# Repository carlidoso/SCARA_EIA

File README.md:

Repositorio para el codigo y material de utilidad del robot SCARA de la universidad EIA

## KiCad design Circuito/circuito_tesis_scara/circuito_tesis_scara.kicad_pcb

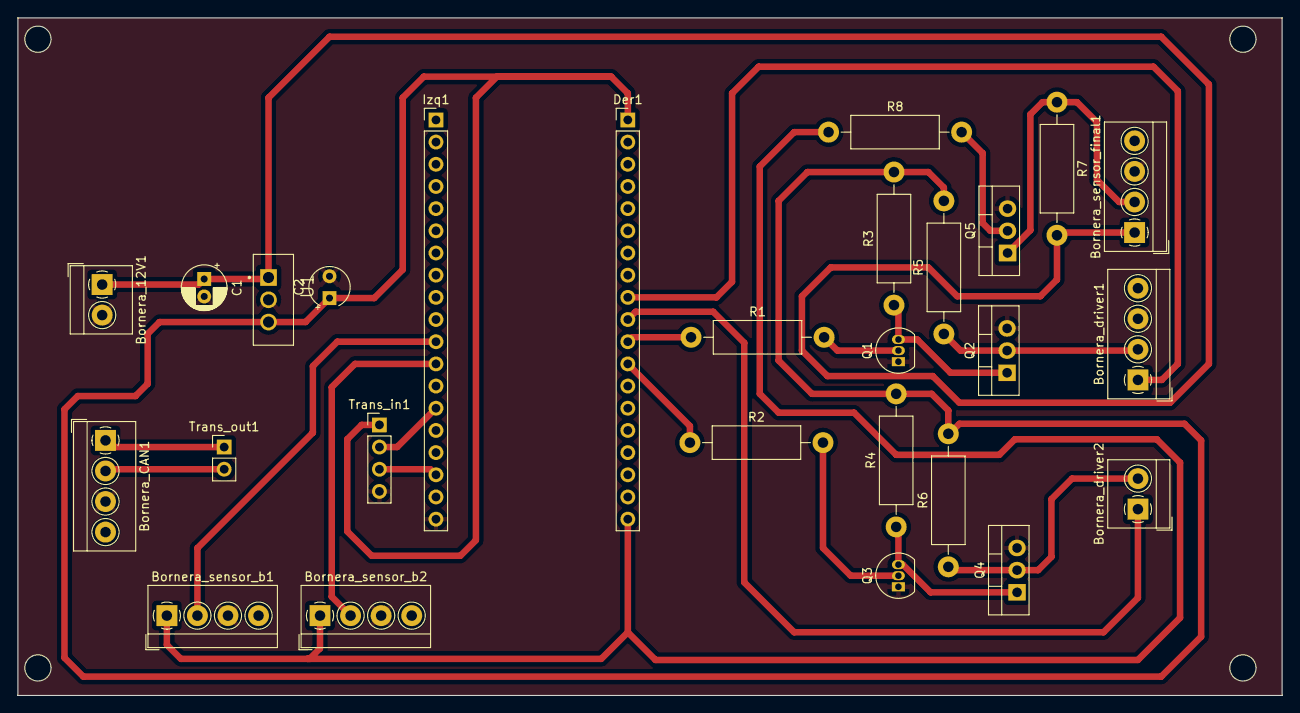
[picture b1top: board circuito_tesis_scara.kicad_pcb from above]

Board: 2 copper layers, 144.8 x 77.6 mm, 27 parts (0 on the bottom side), 22 nets.

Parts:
Bornera_12V1: Screw_Terminal_01x02; TerminalBlock_4Ucon_1x02_P3.50mm_Horizontal
Bornera_CAN1: Screw_Terminal_01x04; TerminalBlock_4Ucon_1x04_P3.50mm_Horizontal
Bornera_driver1: Screw_Terminal_01x04; TerminalBlock_4Ucon_1x04_P3.50mm_Horizontal
Bornera_driver2: Screw_Terminal_01x02; TerminalBlock_4Ucon_1x02_P3.50mm_Horizontal
Bornera_sensor_b1, Bornera_sensor_b2: Screw_Terminal_01x04; TerminalBlock_4Ucon_1x04_P3.50mm_Horizontal
Bornera_sensor_final1: Screw_Terminal_01x04; TerminalBlock_4Ucon_1x04_P3.50mm_Horizontal
C1: C_Polarized; CP_Radial_D5.0mm_P2.00mm
C2: C; CP_Radial_Tantal_D4.5mm_P2.50mm
Der1: Conn_01x19; PinHeader_1x19_P2.54mm_Vertical
Izq1: Conn_01x19; PinHeader_1x19_P2.54mm_Vertical
Q1, Q3: 2N3904; TO-92_Inline
Q2, Q4, Q5: IRF740; TO-220-3_Vertical
R1, R2, R3, R4, R8: 220; R_Axial_DIN0411_L9.9mm_D3.6mm_P15.24mm_Horizontal
R5, R6: 51; R_Axial_DIN0411_L9.9mm_D3.6mm_P15.24mm_Horizontal
R7: 1k; R_Axial_DIN0411_L9.9mm_D3.6mm_P15.24mm_Horizontal
Trans_in1: Conn_01x04; PinHeader_1x04_P2.54mm_Vertical
Trans_out1: Conn_01x02; PinHeader_1x02_P2.54mm_Vertical
U1: L7805CV; TO255P1040X460X1968-3

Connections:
3v3: Bornera_sensor_b1.1, Bornera_sensor_b2.1, Der1.19, R8.1
5v: C2.1, Der1.1, R3.2, R4.2, R5.2, R6.2, Trans_in1.1, U1.3 (OUTPUT)
12v: Bornera_12V1.1, Bornera_sensor_final1.1, C1.1, R7.2, U1.1 (INPUT)
Earth: Bornera_12V1.2, Bornera_CAN1.3, Bornera_driver1.3, Bornera_sensor_b1.3, Bornera_sensor_b2.3, Bornera_sensor_final1.3, C1.2, C2.2, Izq1.19, Q1.1 (E), Q2.3 (S), Q3.1 (E), Q4.3 (S), Q5.3 (S), Trans_in1.4, U1.2 (GROUND)
unnamed: Bornera_CAN1.1, Trans_out1.1
unnamed: Bornera_CAN1.2, Trans_out1.2
unnamed: Bornera_driver1.1, Der1.9
unnamed: Bornera_driver1.2, Q2.2 (D), R5.1
unnamed: Bornera_driver2.1, Der1.10
unnamed: Bornera_driver2.2, Q4.2 (D), R6.1
unnamed: Bornera_sensor_b1.2, Izq1.11
unnamed: Bornera_sensor_b2.2, Izq1.12
unnamed: Bornera_sensor_final1.2, Q5.1 (G), R7.1
unnamed: Der1.8, Q5.2 (D), R8.2
unnamed: Der1.11, R1.1
unnamed: Der1.12, R2.1
unnamed: Izq1.14, Trans_in1.2
unnamed: Izq1.17, Trans_in1.3
unnamed: Q1.2 (B), R1.2
unnamed: Q1.3 (C), Q2.1 (G), R3.1
unnamed: Q3.2 (B), R2.2
unnamed: Q3.3 (C), Q4.1 (G), R4.1

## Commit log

2024-11-12 Create Nexos
2024-11-12 Espacios de trabajo ROS2 y ESP32
